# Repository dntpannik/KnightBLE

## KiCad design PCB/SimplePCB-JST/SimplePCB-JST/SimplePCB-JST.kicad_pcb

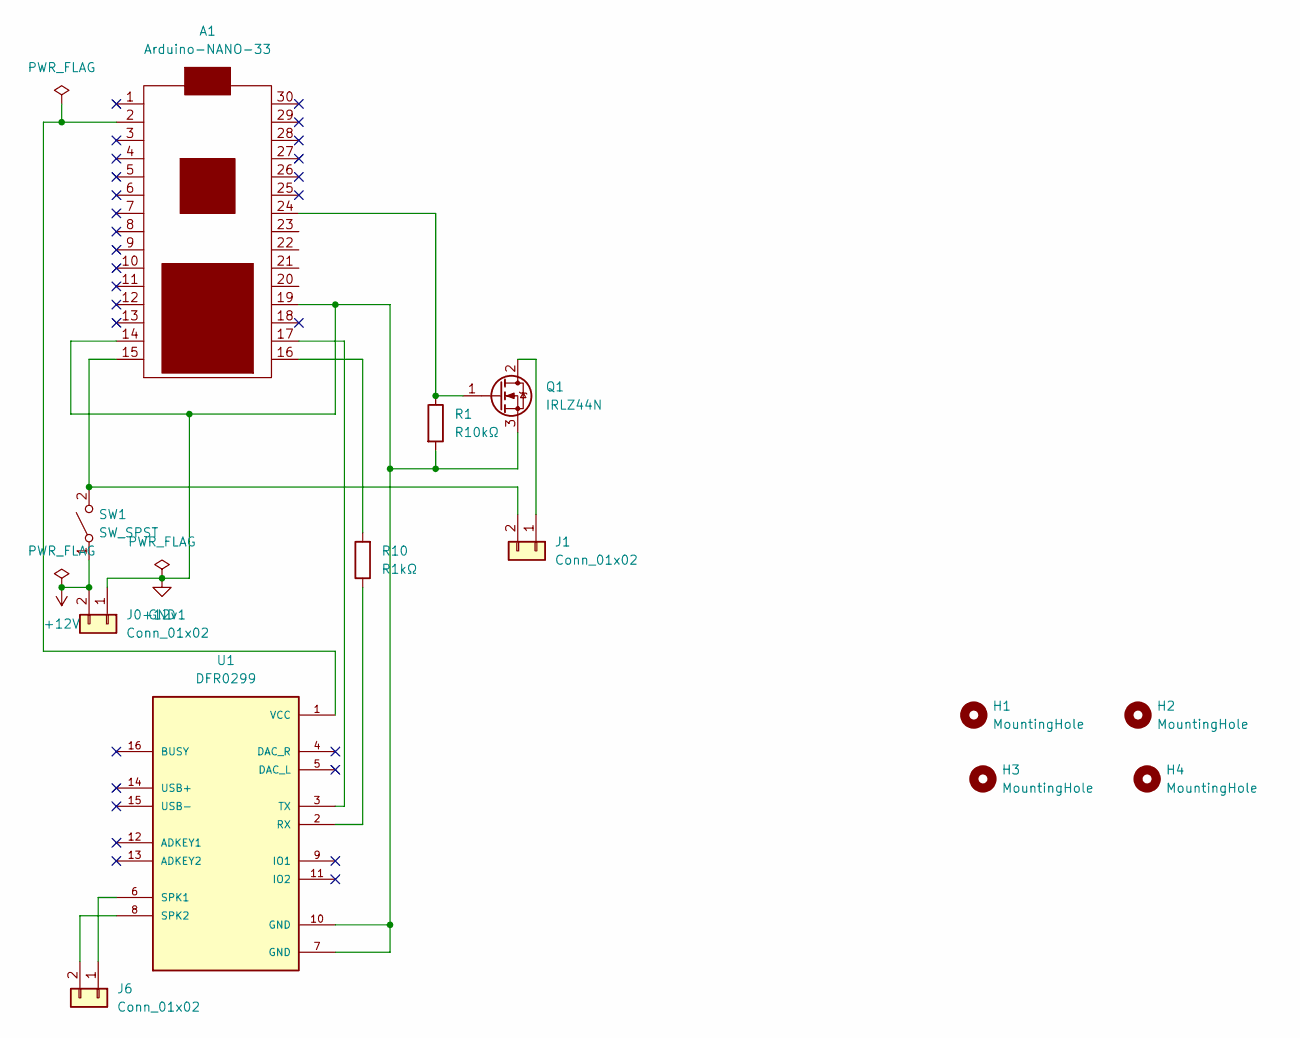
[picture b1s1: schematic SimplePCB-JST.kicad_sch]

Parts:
A1: Arduino-NANO-33; NANO_33_Socket_Castell
H1, H2, H3, H4: MountingHole; MountingHole_2.5mm
J0+12v1, J1, J6: Conn_01x02; JST_PH_B2B-PH-K_1x02_P2.00mm_Vertical
Q1: IRLZ44N; TO-220-3_Vertical
R1: R10kΩ; R_Axial_DIN0207_L6.3mm_D2.5mm_P7.62mm_Horizontal
R10: R1kΩ; R_Axial_DIN0207_L6.3mm_D2.5mm_P7.62mm_Horizontal
SW1: SW_SPST; SW_CW_GPTS203211B
U1: DFR0299; MODULE_DFR0299

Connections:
+12V: J0+12v1.2, SW1.1 (A)
GND: A1.14 (GND), A1.19 (GND), J0+12v1.1, Q1.3 (S), R1.2, U1.7 (GND), U1.10 (GND)
unnamed: A1.2 (+3V3), U1.1 (VCC)
unnamed: A1.15 (VIN), J1.2, SW1.2 (B)
unnamed: A1.16 (TX), R10.2
unnamed: A1.17 (RX), U1.3 (TX)
unnamed: A1.24 (~D6), Q1.1 (G), R1.1
unnamed: J1.1, Q1.2 (D)
unnamed: J6.1, U1.6 (SPK1)
unnamed: J6.2, U1.8 (SPK2)
unnamed: R10.1, U1.2 (RX)

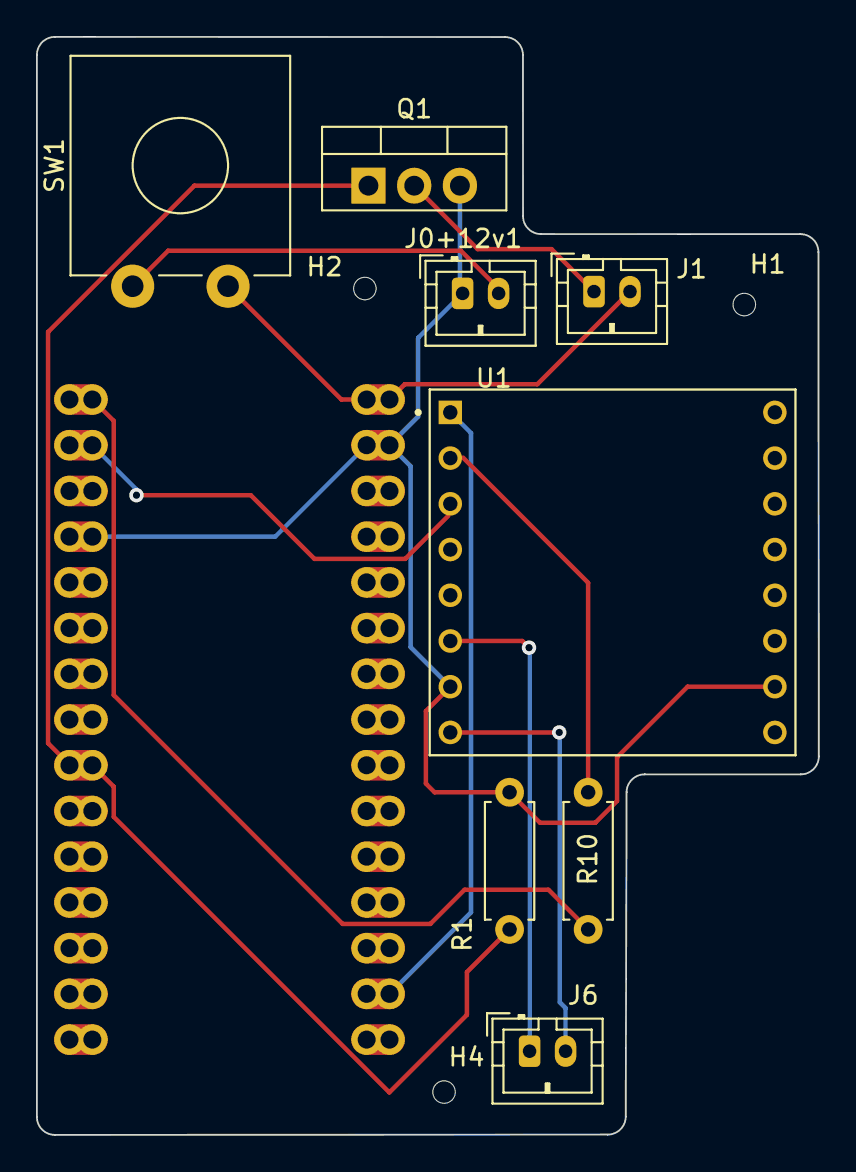
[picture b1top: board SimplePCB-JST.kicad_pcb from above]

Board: 2 copper layers, 43.4 x 61.0 mm, 12 parts (0 on the bottom side), 11 nets.

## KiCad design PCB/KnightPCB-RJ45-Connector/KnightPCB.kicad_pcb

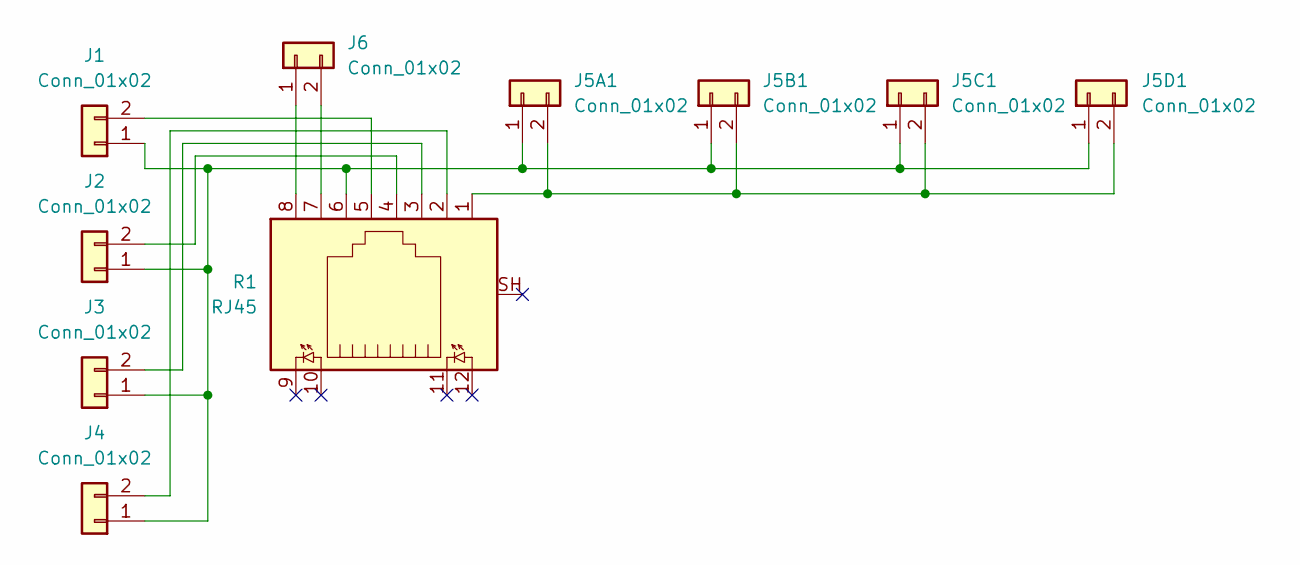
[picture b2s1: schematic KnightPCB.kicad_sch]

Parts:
J1, J2, J3, J4, J5A1, J5B1, J5C1, J5D1, J6: Conn_01x02; JST_PH_B2B-PH-K_1x02_P2.00mm_Vertical
R1: RJ45; RJ45_BEL_SS74301-00x_Vertical

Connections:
unnamed: J1.2, R1.5
unnamed: J2.2, R1.4
unnamed: J3.2, R1.3
unnamed: J4.2, R1.2
unnamed: J1.1, J2.1, J3.1, J4.1, J5A1.1, J5B1.1, J5C1.1, J5D1.1, R1.6
unnamed: J5A1.2, J5B1.2, J5C1.2, J5D1.2, R1.1
unnamed: J6.1, R1.8
unnamed: J6.2, R1.7

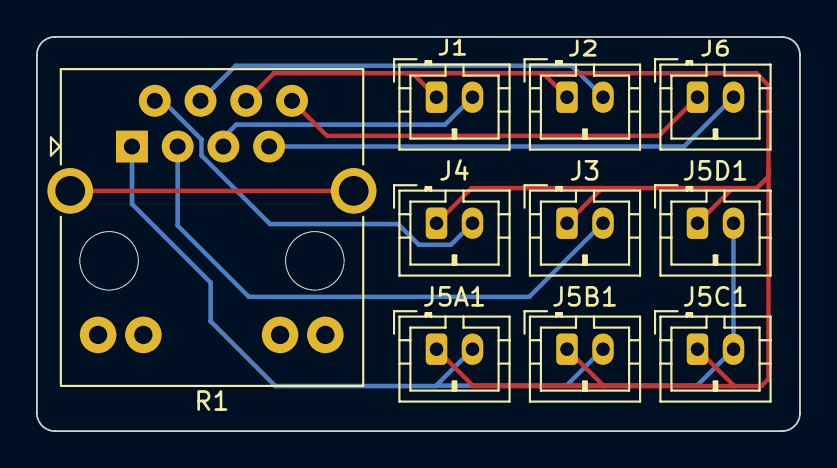
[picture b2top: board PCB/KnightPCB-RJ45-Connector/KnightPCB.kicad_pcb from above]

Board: 2 copper layers, 42.4 x 21.9 mm, 10 parts (0 on the bottom side), 8 nets.

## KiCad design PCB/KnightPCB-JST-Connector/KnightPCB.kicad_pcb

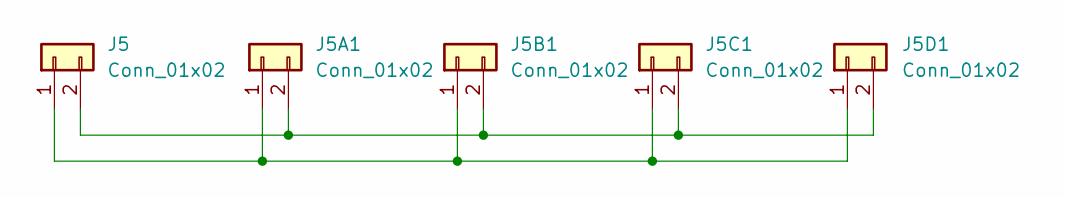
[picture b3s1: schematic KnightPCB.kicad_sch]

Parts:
J5, J5A1, J5B1, J5C1, J5D1: Conn_01x02; JST_PH_B2B-PH-K_1x02_P2.00mm_Vertical

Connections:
unnamed: J5.1, J5A1.1, J5B1.1, J5C1.1, J5D1.1
unnamed: J5.2, J5A1.2, J5B1.2, J5C1.2, J5D1.2

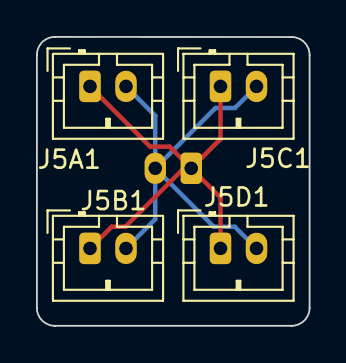
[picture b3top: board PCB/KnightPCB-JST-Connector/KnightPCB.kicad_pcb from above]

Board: 2 copper layers, 15.1 x 16.1 mm, 5 parts (1 on the bottom side), 2 nets.

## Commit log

2022-04-29 Working mostly
2022-04-29 Work
2022-04-30 Cleaned up
2022-04-30 fixed name
2022-04-30 adding more support
2022-04-30 Added arduino
2022-04-30 Added horn audio
2022-04-30 Fixed build issue
2022-05-01 Added icon. Messing with code for speakers
2022-05-01 Moved some files
2022-05-02 updated icons, some work
2022-07-17 Audio, Adruino updates, doc updates
2023-02-11 KiKad PCB
2023-02-11 gitignore
2023-07-05 Changes & Knight Control
2023-07-05 3d files
2023-07-05 cleanup
2023-07-19 arduino
2023-09-20 Updates for cerastus
2023-09-20 Added Cerastus base
2023-09-25 test
2023-09-30 Storm of Wrath
2023-10-02 model updates
2023-10-05 Cerastus Acheron changes
2023-10-15 Knight
2024-03-14 Porphyrion updates
2024-03-14 pory updates
